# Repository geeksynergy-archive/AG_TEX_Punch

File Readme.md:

AGTEX is a Jacquard punching card tool software solution,
It contains all the required tools integrated into one set

The following lists all the features in the AGTEX.
GC-Punch: Designed for the AG-TEX this was the first industrial project undertaken.
It was an end to end system development for Jacquard Punching card system which 
included development of interfacing board for the legacy system i.e the control net and a 
fully-fledged software tool that incorporates works and not limited to perform bit 
manipulation of the image, image to card layout conversion as addressed below.,

 *. Fast Lane Project with 1 month development time and 1 month testing.

 *. Complete image to card solution, unique in industry

 *. Built as two models

		*. Version-1 as simplistic and tightly constrained to get maximum out of GPIO and I2C pins with ATMega8

		*. Version-2 was designed using ATMega2560 to have higher degree of flexibility and much more real-time response.

 *. UI was built on GUIDE with Mathworks Matlab.

 *. Backend Code handling was done on Matlab and ported to .Net C#.

 *. Associated work includes PCB design and fabrication which was a shield 
for Arduino Mega2560

 *. Legacy System was analysed to be digitally rewired using DSLogix Pro.

 *. Deployment has been done using WiX – Windows Installer XML.

 *. Unique Hardware Locking on the Microcontroller to avoid tampering.

 *. Standalone no-computer required for servicing, testing and test-card 
printing.

 *. Auto Rack Reset to prevent mechanical rack dislodging.

 *. Extensibility option to print card numbers.

 *. Various security features including auto-stop on card breakage, card 
blockage or card mismatch.

 *. Auto-Card Layout detection and selection for any template image size.

 *. Custom Card layout functionality for user defined card layouts.

 *. Fully compatible keyboard shortcuts for software device testing.

 *. Supports OS from XP to Windows-X

 *. x64 as well as x86 compatible.

 *. Fully Customizable print head punch pattern.

 *. Custom Card printing for missing designs and broken cards.

 *. Card advance and recede options for quick seek and printing.

 *. Emergency Holes for added design benefits.

 *. Auto Lacing Detection and addition for cards of higher pin count.

 *. One click updateable firmware for future releases.

Since most of the existing customers of AG-TEX had a legacy control-net and were using 
DOS based machine, the key conditions that were taken to the drawing table were

1. Keep the user experience simple and in-close relation to that of one which was 
already existing.
2. Minimum/No hardware changes to the existing control net.
3. Simple and Low-power consumption hardware addition for the interface.

Keeping the above requirement as the priority guidelines the design was drawn, the initial 
prototyping was done using AT-Mega 8 / 328 to minimize the cost and footprint of the 
interface board, the testing was done successfully under first 15days of the project 
development lifecycle.

Once the client FS requirement was thawed to address the need of a physical keypad by 
the customers to allow quick access to the testing functionality on a standalone system, 
the device was redesigned to work with ATMEGA-2560 microcontroller there by 
providing additional functionalities of displaying current actions on a LCD display and 
provide the indication lights for software/hardware modes of operation.

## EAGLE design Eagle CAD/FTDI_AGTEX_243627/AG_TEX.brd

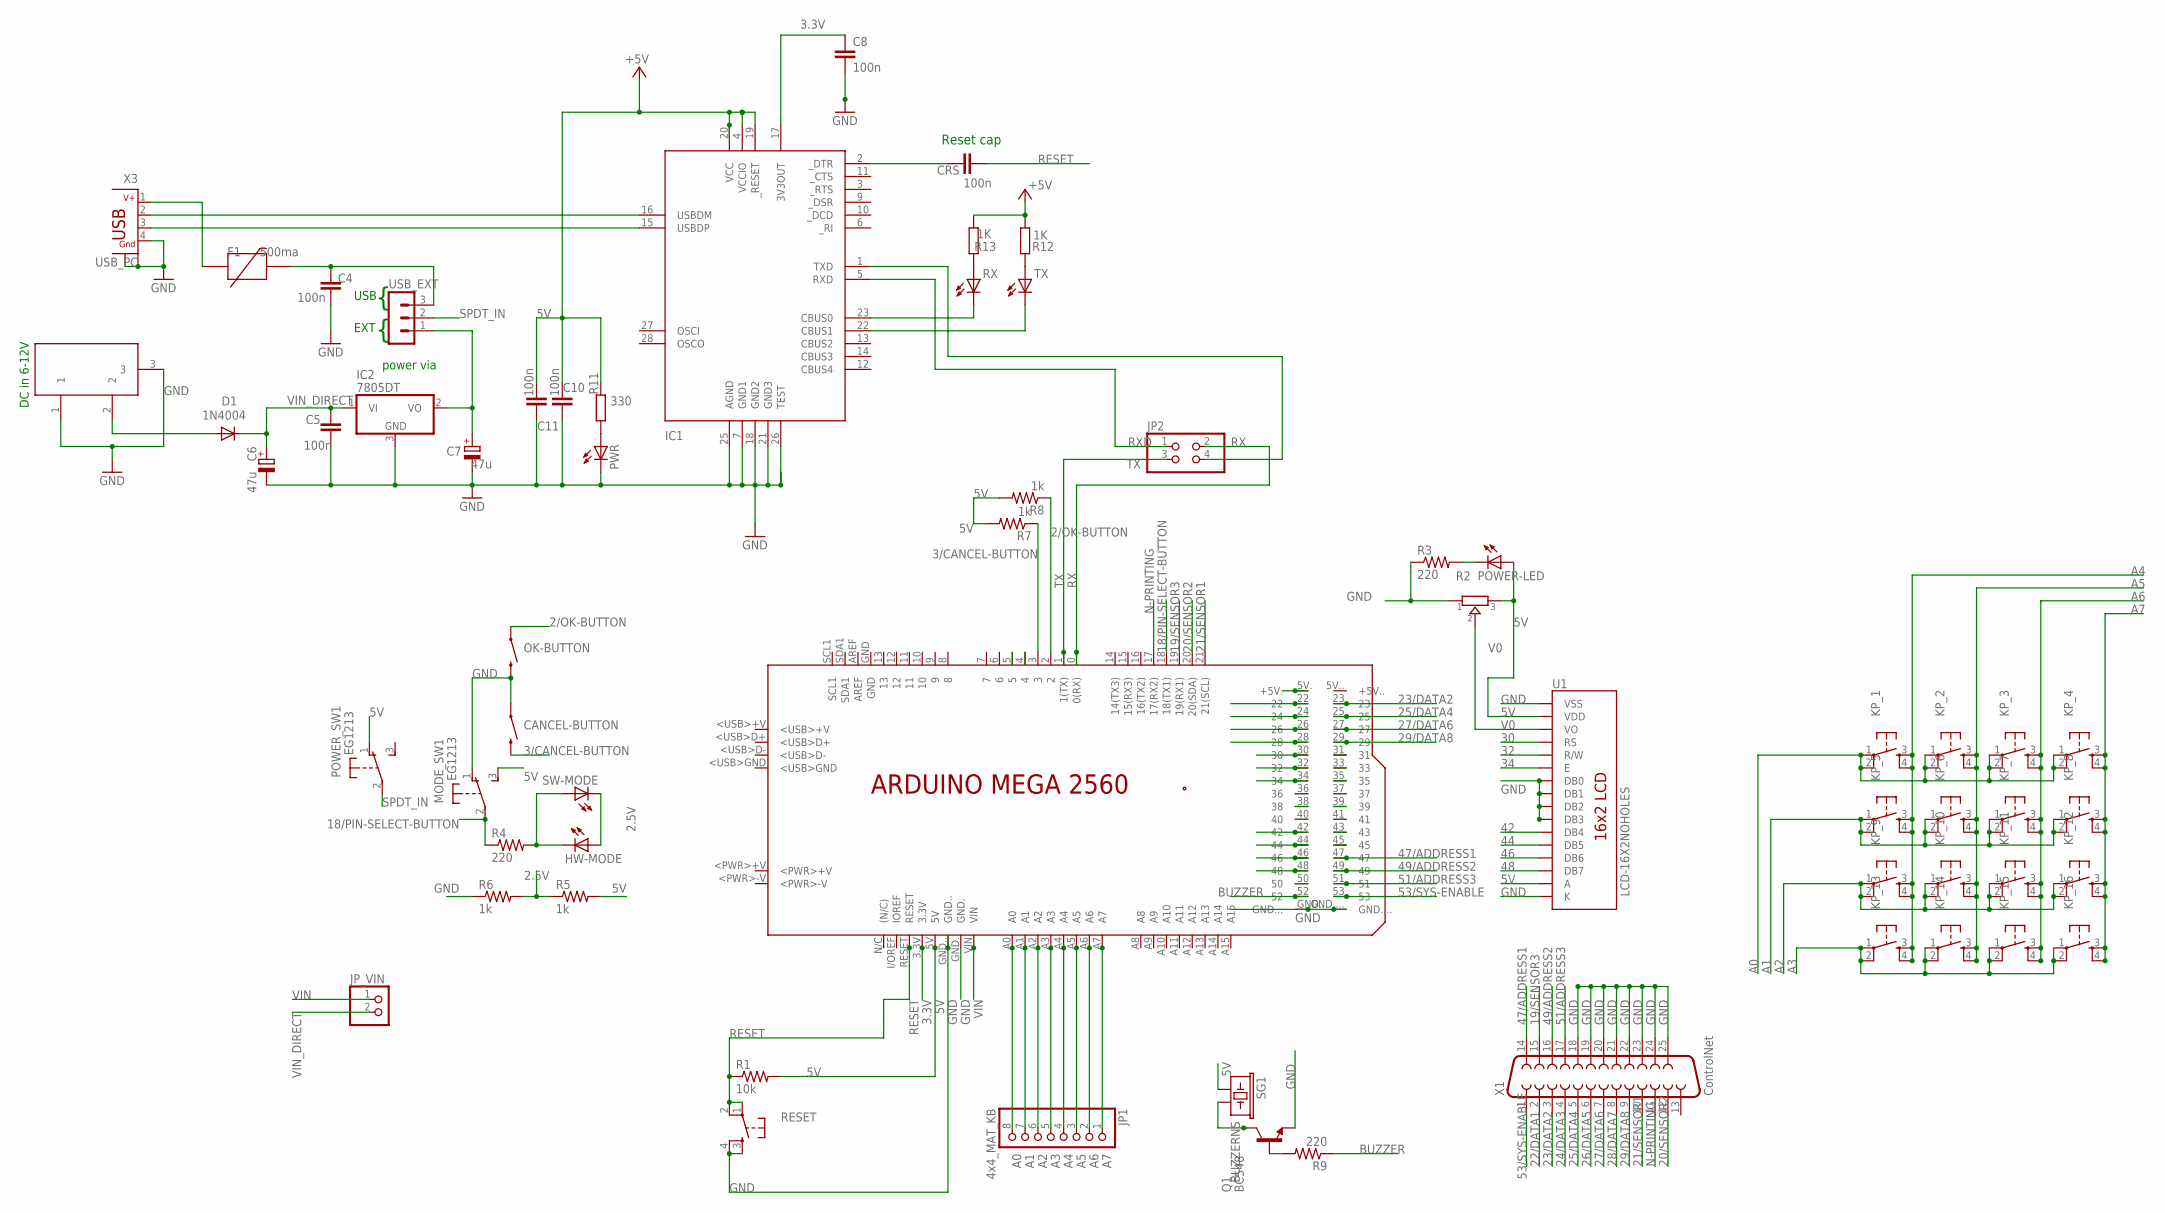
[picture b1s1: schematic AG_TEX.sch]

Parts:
C4, C5, C8, C10: 100n; C050-024X044
C6, C7: 47u; E3,5-8
C11: 100n; C1206
CANCEL-BUTTON: SWITCH-MOMENTARY-212MM; TACTILE-PTH-12MM
CRS: 100n; C050-024X044
D1: 1N4004; DIODE-0.4
DC1: 9V in; DC-21MM
F1: 500ma; PTC
HW-MODE: LED5MM
IC1: FT232RL; SSOP28DB
IC2: 7805DT; TO252
JP1: 4x4_MAT_KB; 1X08-CLEANBIG
JP2: PINHD-2X2; 2X02
JP_VIN: PINHD-1X2; 1X02
KP_1, KP_2, KP_3, KP_4, KP_5, KP_6, KP_7, KP_8, KP_9, KP_10, KP_11, KP_12, KP_13, KP_14, KP_15, KP_16: TAC_SWITCHPTH; TACTILE-PTH
MODE_SW: EG1213
OK-BUTTON: SWITCH-MOMENTARY-212MM; TACTILE-PTH-12MM
PCB1: ARDUINO_MEGA2560
POWER-LED: LED5MM
POWER_SW: EG1213
PWR: LED3MM
Q1: BC548; TO92-EBC
R1: 10k; 0204/7
R2: TRIMMER-3306F; TRIMMER_3306F
R3, R4, R9: 220; 0204/7
R5, R6, R7, R8: 1k; 0204/7
R11: 330; 0204/7
R12, R13: 1K; 0204/7
RESET: TAC_SWITCHPTH; TACTILE-PTH
RX: LED3MM
SG1: BUZZERNS; BUZZER-12MM-NS
SW-MODE: LED5MM
TX: LED3MM
U1: LCD-16X2NOHOLES; LCD-16X2_NOHOLES
USB_EXT: MA03-1
X1: ControlNet; F25HP
X3: USB_PC; USB-WSHIELDPADS

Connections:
2.5V: HW-MODE.A, R5.1, R6.2, SW-MODE.K (C)
2/OK-BUTTON: OK-BUTTON.1, PCB1.2, R8.1
3.3V: C8.1, IC1.17 (3V3OUT), PCB1.3.3V
3/CANCEL-BUTTON: CANCEL-BUTTON.3 (2), PCB1.3, R7.1
4: PCB1.4
5: PCB1.5
5V: C10.2, C11.2, IC1.4 (VCCIO), IC1.19 (_RESET), IC1.20 (VCC), MODE_SW.3 (S), PCB1.5V, PCB1.5V. (+5V.), POWER-LED.A, POWER_SW.1 (O), R1.2, R2.3, R5.2, R7.2, R8.2, R11.1, R12.1, R13.1, SG1.+ (1), U1.2 (VDD), U1.15 (A)
18/PIN-SELECT-BUTTON: MODE_SW.2, PCB1.18 (18(TX1)), R4.1
19/SENSOR3: PCB1.19 (19(RX1)), X1.15
20/SENSOR2: PCB1.20 (20(SDA)), X1.12
21/SENSOR1: PCB1.21 (21(SCL)), X1.10
22/DATA1: PCB1.22, X1.2
23/DATA2: PCB1.23, X1.3
24/DATA3: PCB1.24, X1.4
25/DATA4: PCB1.25, X1.5
26/DATA5: PCB1.26, X1.6
27/DATA6: PCB1.27, X1.7
28/DATA7: PCB1.28, X1.8
29/DATA8: PCB1.29, X1.9
30: PCB1.30, U1.4 (RS)
31: PCB1.31
32: PCB1.32, U1.5 (R/W)
33: PCB1.33
34: PCB1.34, U1.6 (E)
35: PCB1.35
36: PCB1.36
37: PCB1.37
38: PCB1.38
39: PCB1.39
40: PCB1.40
41: PCB1.41
42: PCB1.42, U1.11 (DB4)
43: PCB1.43
44: PCB1.44, U1.12 (DB5)
45: PCB1.45
46: PCB1.46, U1.13 (DB6)
47/ADDRESS1: PCB1.47, X1.14
48: PCB1.48, U1.14 (DB7)
49/ADDRESS2: PCB1.49, X1.16
50: PCB1.50
51/ADDRESS3: PCB1.51, X1.17
53/SYS-ENABLE: PCB1.53, X1.1
A0: JP1.8, KP_1.1, KP_1.2, KP_2.1, KP_2.2, KP_3.1, KP_3.2, KP_4.1, KP_4.2, PCB1.A0
A1: JP1.7, KP_5.1, KP_5.2, KP_6.1, KP_6.2, KP_7.1, KP_7.2, KP_8.1, KP_8.2, PCB1.A1
A2: JP1.6, KP_9.1, KP_9.2, KP_10.1, KP_10.2, KP_11.1, KP_11.2, KP_12.1, KP_12.2, PCB1.A2
A3: JP1.5, KP_13.1, KP_13.2, KP_14.1, KP_14.2, KP_15.1, KP_15.2, KP_16.1, KP_16.2, PCB1.A3
A4: JP1.4, KP_1.3, KP_1.4, KP_5.3, KP_5.4, KP_9.3, KP_9.4, KP_13.3, KP_13.4, PCB1.A4
A5: JP1.3, KP_2.3, KP_2.4, KP_6.3, KP_6.4, KP_10.3, KP_10.4, KP_14.3, KP_14.4, PCB1.A5
A6: JP1.2, KP_3.3, KP_3.4, KP_7.3, KP_7.4, KP_11.3, KP_11.4, KP_15.3, KP_15.4, PCB1.A6
A7: JP1.1, KP_4.3, KP_4.4, KP_8.3, KP_8.4, KP_12.3, KP_12.4, KP_16.3, KP_16.4, PCB1.A7
BUZZER: PCB1.52, R9.1
GND: C4.1, C5.1, C6.-, C7.-, C8.2, C10.1, C11.1, CANCEL-BUTTON.1, DC1.1, DC1.3, IC1.7 (GND1), IC1.18 (GND2), IC1.21 (GND3), IC1.25 (AGND), IC1.26 (TEST), IC2.3 (GND), MODE_SW.1 (O), OK-BUTTON.3 (2), PCB1.GND., PCB1.GND.., PCB1.GND..., PCB1.GND...., PWR.K (C), Q1.E, R2.1, R3.1, R6.1, RESET.3, RESET.4, U1.1 (VSS), U1.7 (DB0), U1.8 (DB1), U1.9 (DB2), U1.10 (DB3), U1.16 (K), X1.18, X1.19, X1.20, X1.21, X1.22, X1.23, X1.24, X1.25, X3.4, X3.SH1 (GND), X3.SH2 (GND)
JACK_USB_V+: D1.A, DC1.2
unnamed: Q1.C, SG1.- (2)
unnamed: Q1.B, R9.2
unnamed: POWER-LED.K (C), R3.2
unnamed: HW-MODE.K (C), R4.2, SW-MODE.A
unnamed: PWR.A, R11.2
unnamed: CRS.1, IC1.2 (_DTR)
unnamed: IC1.16 (USBDM), X3.2
unnamed: IC1.15 (USBDP), X3.3
unnamed: R12.2, TX.A
unnamed: R13.2, RX.A
N-PRINTING: PCB1.17 (17(RX2)), X1.11
RESET: CRS.2, PCB1.RESET, R1.1, RESET.1, RESET.2
RX: JP2.2, PCB1.0 (0(RX))
RXD: IC1.5 (RXD), JP2.1
RXLED: IC1.22 (CBUS1), TX.K (C)
SPDT_EXT: C7.+, IC2.2 (VO), USB_EXT.1
SPDT_IN: POWER_SW.2, USB_EXT.2
TX: JP2.3, PCB1.1 (1(TX))
TXD: IC1.1 (TXD), JP2.4
TXLED: IC1.23 (CBUS0), RX.K (C)
USB_V+: F1.P$1 (1), X3.1
USB_V++: C4.2, F1.P$2 (2), USB_EXT.3
V0: R2.2, U1.3 (VO)
VIN: JP_VIN.1, PCB1.VIN
VIN_DIRECT: C5.2, C6.+, D1.C, IC2.1 (VI), JP_VIN.2

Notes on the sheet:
EXT
USB
power via
Reset cap
DC in 6-12V

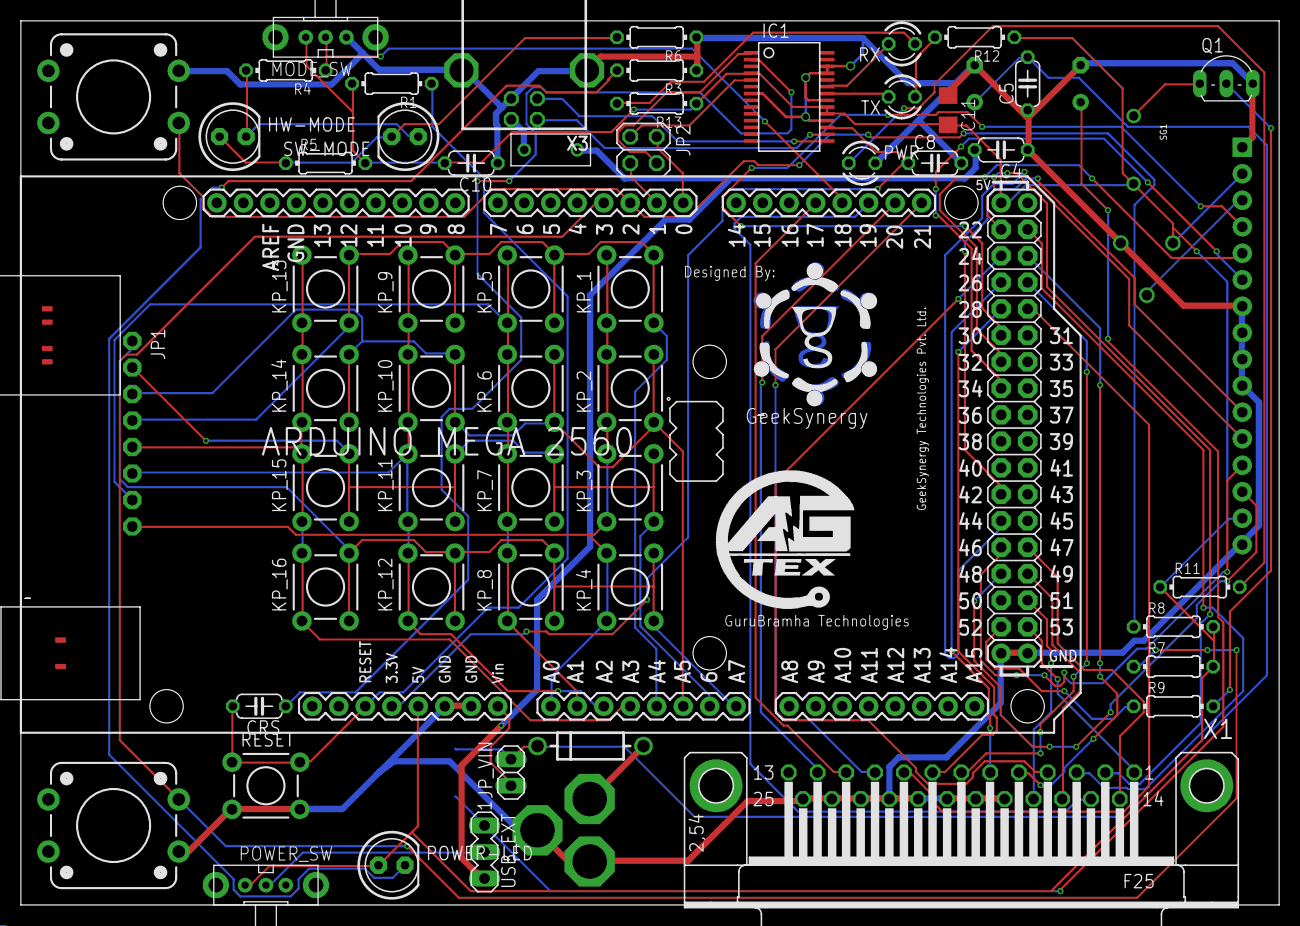
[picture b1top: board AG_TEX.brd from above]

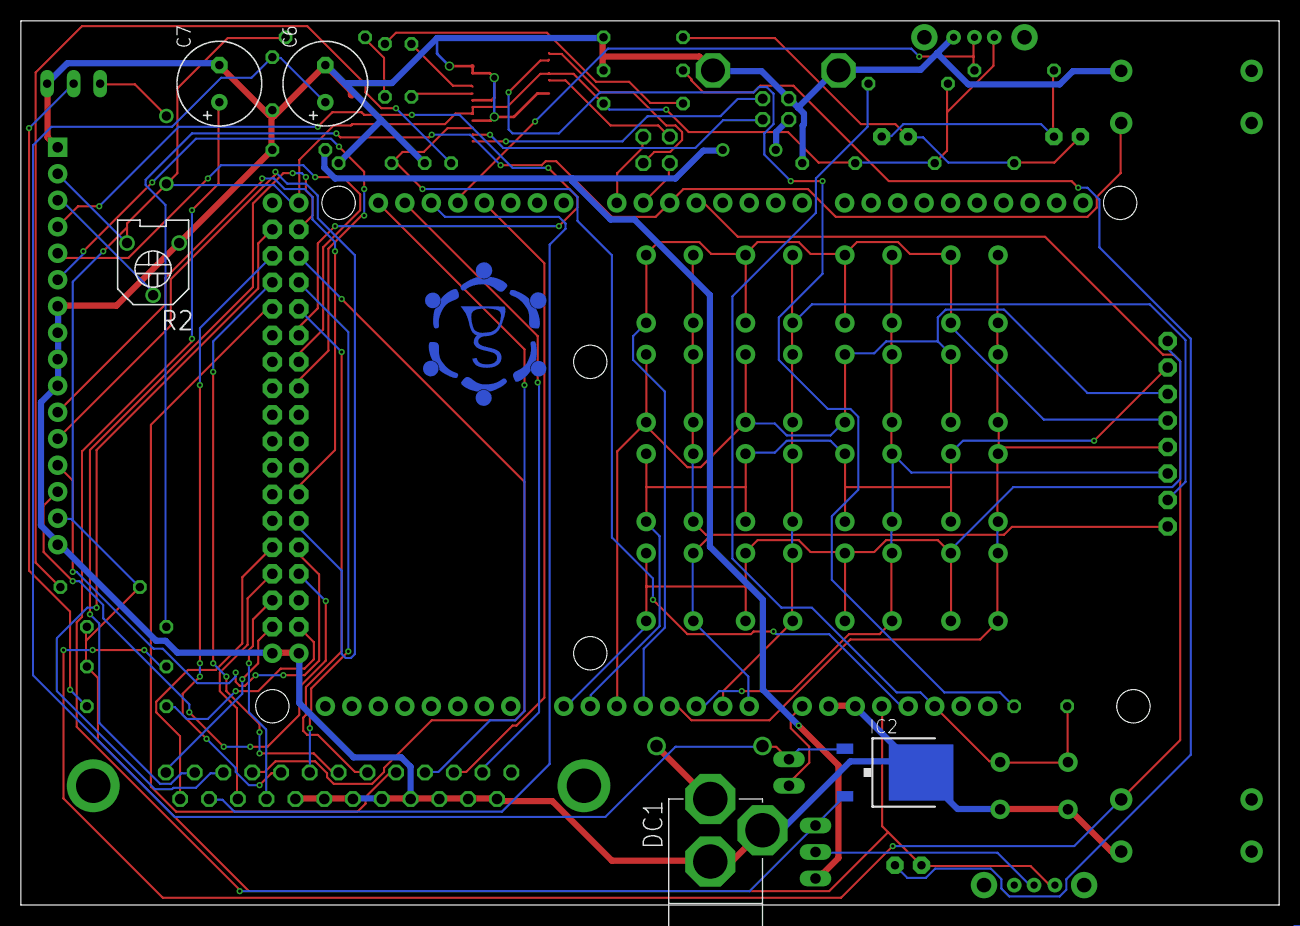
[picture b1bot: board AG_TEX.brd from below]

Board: 2 copper layers, 120.6 x 84.8 mm, 62 parts (5 on the bottom side), 64 nets.

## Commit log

2015-09-17 :octocat: Added .gitattributes & .gitignore files
2015-09-17 First Commit
    Added New Arduino Libraries and Mat Files along with Splash Images and
    Template Cards
2015-09-17 Drivers Set Updated
    CH340, FTDI, SILLABS CP2102, Arduino and ZADIG updated
2015-09-17 Added Readme file
    Added project readme file
2015-09-17 CardType updated
    Modified 612, 828 card lacing points
    added custom card layouts and full punch cards for both
2015-09-17 Readme ReFormatted
    Readme ReFormatted
2015-09-17 Reformatted Readme
    reformatted Readme
2015-09-17 Eagle CAD addition
    Added Gerbers and CAD files
2015-10-14 UI and Arduino Code updated for new boards
    Update UI Handler to speed up the process
2015-12-03 Updated Licensor and Support code from Sachins Code
    Updated Licensor with all fiunctionality and Support code from Sachins
    Code
2015-12-08 Dot Net Licensor with Windows SDK
    Although not perfect all modifications are hidden in easter eggs and
    comments till further payment
2016-02-08 Update Full Time License
    Updated C# code removed all limitation and furnished UI
2016-02-09 License Revised to Show Status
    Now status of the license shows at the bottom

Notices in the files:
parts and their libraries:
SparkFun: Licensing: CC v3.0 Share-Alike You are welcome to use this library for commercial purposes.
SparkFun-Displays: Licensing: Creative Commons ShareAlike 4.0 International - https://creativecommons.org/licenses/by-sa/4.0
